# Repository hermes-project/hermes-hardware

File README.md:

# hermes-hardware
# Authors : François Charles, Simon Ménard, Raphaël Outhier

This repository lists all you need if you're interested in the robot hardware's architecture.

What you may find in this repository :

-the 3D models designed with SolidWorks CAD;

-the Eagle CAD PCB schematics and board layout

-the Eagle CAD libraries used

-the datasheets of electronic components

-documentation about how to drive the robot successfully (in French at the moment :p English version to come)

Enjoy your trip among these files ! :)

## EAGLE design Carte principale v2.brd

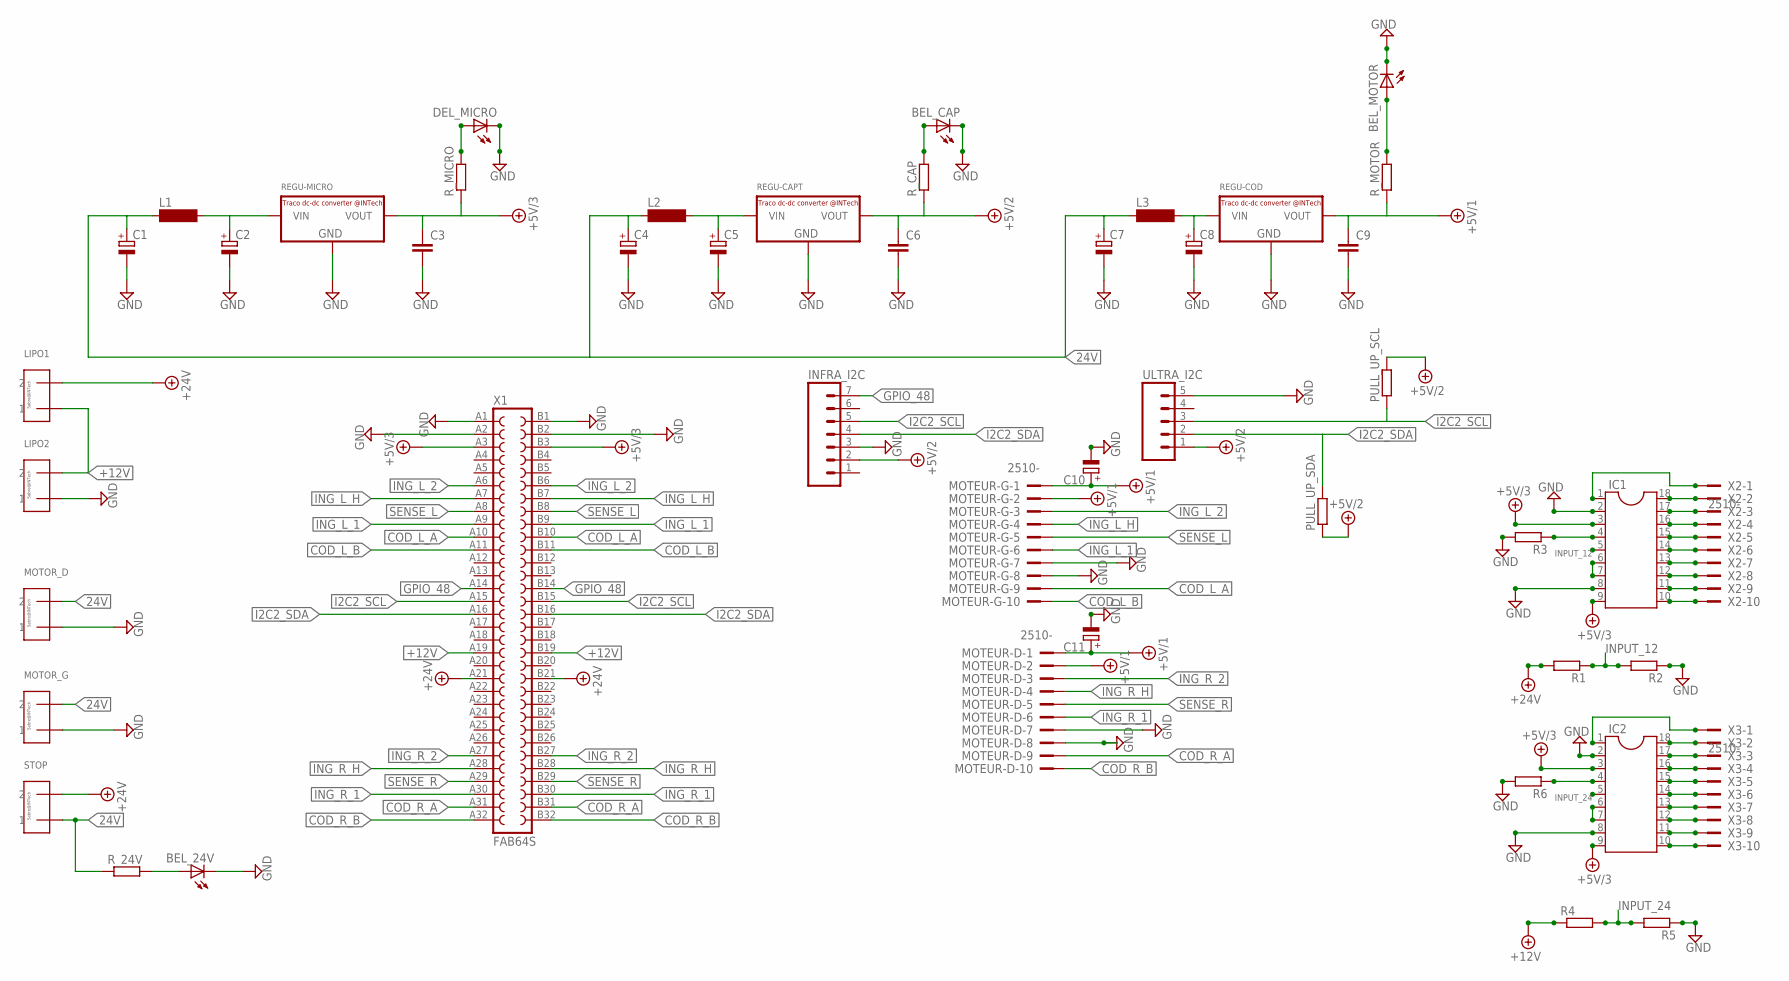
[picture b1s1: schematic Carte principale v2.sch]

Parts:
BEL_24V: LED5MM
BEL_CAP: LED5MM
BEL_MOTOR: LED5MM
C1, C2, C4, C5, C7, C8, C10, C11: CPOL-EUE2.5-6; E2,5-6
C3, C6: C-EU050-025X075; C050-025X075
C9: C5/3; C5B3
DEL_MICRO: LED5MM
IC1, IC2: DIL18S; SOCKET-18
INFRA_I2C: M07; 07P
L1, L2, L3: SD12-1000; SD12_1000
LIPO1, LIPO2: 43160
MOTEUR-D: 2510-; PAK100/2500-10
MOTEUR-G: 2510-; PAK100/2500-10
MOTOR_D: 43160
MOTOR_G: 43160
PULL_UP_SCL: R-EU_0204/7; 0204/7
PULL_UP_SDA: R-EU_0204/7; 0204/7
R1, R2, R3, R4, R5, R6: R-EU_0204/7; 0204/7
REGU-CAPT: R-78C-1.0_INTECH; SIP3_INTECH
REGU-COD: R-78C-1.0_INTECH; SIP3_INTECH
REGU-MICRO: R-78C-1.0_INTECH; SIP3_INTECH
R_24V: R-EU_0204/7; 0204/7
R_CAP: R-EU_0204/7; 0204/7
R_MICRO: R-EU_0204/7; 0204/7
R_MOTOR: R-EU_0204/7; 0204/7
STOP: 43160
ULTRA_I2C: M05; 05P
X1: FAB64S
X2, X3: 2510-; PAK100/2500-10

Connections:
24V: C1.+, C4.+, C7.+, L1.1, L2.1, L3.1, MOTOR_D.2_1 (2), MOTOR_D.2_2 (2), MOTOR_G.2_1 (2), MOTOR_G.2_2 (2), R_24V.1, STOP.1_1 (1), STOP.1_2 (1)
+5V/1: C9.1, C10.+, C11.+, MOTEUR-D.1, MOTEUR-D.2, MOTEUR-G.1, MOTEUR-G.2, REGU-COD.VOUT, R_MOTOR.1
+5V/2: C6.1, INFRA_I2C.2, PULL_UP_SCL.2, PULL_UP_SDA.1, REGU-CAPT.VOUT, R_CAP.1, ULTRA_I2C.1
+5V/3: C3.1, IC1.3, IC1.9, IC2.3, IC2.9, REGU-MICRO.VOUT, R_MICRO.1, X1.A3, X1.B3
+12V: LIPO1.1_1 (1), LIPO1.1_2 (1), LIPO2.2_1 (2), LIPO2.2_2 (2), R4.1, X1.A19, X1.B19
+24V: LIPO1.2_1 (2), LIPO1.2_2 (2), R1.2, STOP.2_1 (2), STOP.2_2 (2), X1.A21, X1.B21
COD_L_A: MOTEUR-G.9, X1.A10, X1.B10
COD_L_B: MOTEUR-G.10, X1.A11, X1.B11
COD_R_A: MOTEUR-D.9, X1.A31, X1.B31
COD_R_B: MOTEUR-D.10, X1.A32, X1.B32
GND: BEL_24V.K (C), BEL_CAP.K (C), BEL_MOTOR.K (C), C1.-, C2.-, C3.2, C4.-, C5.-, C6.2, C7.-, C8.-, C9.2, C10.-, C11.-, DEL_MICRO.K (C), IC1.2, IC1.8, IC2.2, IC2.8, INFRA_I2C.3, LIPO2.1_1 (1), LIPO2.1_2 (1), MOTEUR-D.7, MOTEUR-D.8, MOTEUR-G.7, MOTEUR-G.8, MOTOR_D.1_1 (1), MOTOR_D.1_2 (1), MOTOR_G.1_1 (1), MOTOR_G.1_2 (1), R2.1, R3.2, R5.1, R6.2, REGU-CAPT.GND, REGU-COD.GND, REGU-MICRO.GND, ULTRA_I2C.5, X1.A1, X1.A2, X1.B1, X1.B2
GPIO_48: INFRA_I2C.7, X1.A14, X1.B14
I2C2_SCL: INFRA_I2C.5, PULL_UP_SCL.1, ULTRA_I2C.3, X1.A15, X1.B15
I2C2_SDA: INFRA_I2C.4, PULL_UP_SDA.2, ULTRA_I2C.2, X1.A16, X1.B16
ING_L_1: MOTEUR-G.6, X1.A9, X1.B9
ING_L_2: MOTEUR-G.3, X1.A6, X1.B6
ING_L_H: MOTEUR-G.4, X1.A7, X1.B7
ING_R_1: MOTEUR-D.6, X1.A30, X1.B30
ING_R_2: MOTEUR-D.3, X1.A27, X1.B27
ING_R_H: MOTEUR-D.4, X1.A28, X1.B28
INPUT_12: IC1.5, R1.1, R2.2
INPUT_24: IC2.5, R4.2, R5.2
unnamed: DEL_MICRO.A, R_MICRO.2
unnamed: BEL_24V.A, R_24V.2
unnamed: C8.+, L3.2, REGU-COD.VIN
unnamed: C2.+, L1.2, REGU-MICRO.VIN
unnamed: C5.+, L2.2, REGU-CAPT.VIN
unnamed: BEL_CAP.A, R_CAP.2
unnamed: IC1.6, IC1.7
unnamed: IC1.12, X2.8
unnamed: IC1.13, X2.7
unnamed: BEL_MOTOR.A, R_MOTOR.2
unnamed: IC1.17, X2.3
unnamed: IC1.15, X2.5
unnamed: IC1.14, X2.6
unnamed: IC1.11, X2.9
unnamed: IC1.10, X2.10
unnamed: IC1.16, X2.4
unnamed: IC2.6, IC2.7
unnamed: IC1.18, X2.2
unnamed: IC1.1, X2.1
unnamed: IC2.10, X3.10
unnamed: IC2.11, X3.9
unnamed: IC2.12, X3.8
unnamed: IC2.13, X3.7
unnamed: IC2.14, X3.6
unnamed: IC2.15, X3.5
unnamed: IC2.16, X3.4
unnamed: IC2.17, X3.3
unnamed: IC2.18, X3.2
unnamed: IC2.1, X3.1
unnamed: IC1.4, R3.1
unnamed: IC2.4, R6.1
SENSE_L: MOTEUR-G.5, X1.A8, X1.B8
SENSE_R: MOTEUR-D.5, X1.A29, X1.B29

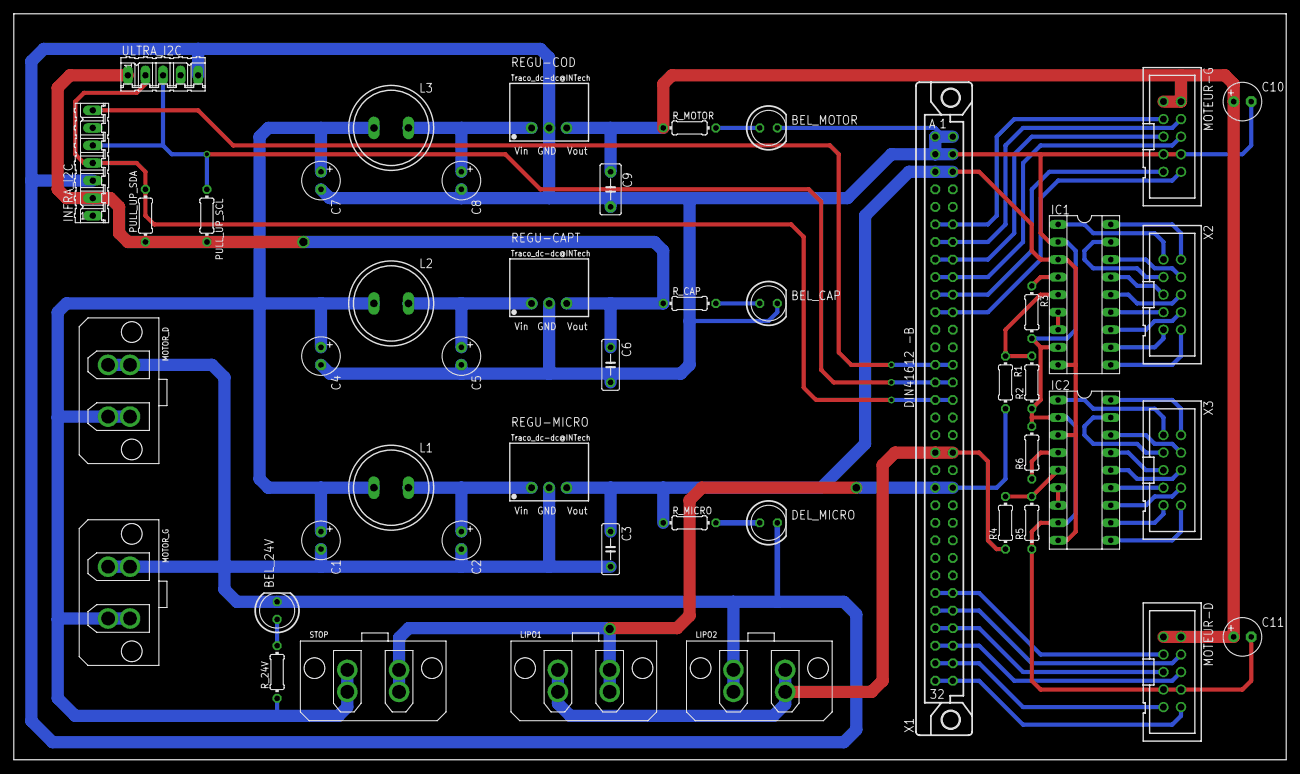
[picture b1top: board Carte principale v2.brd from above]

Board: 2 copper layers, 184.1 x 108.0 mm, 47 parts (0 on the bottom side), 55 nets.

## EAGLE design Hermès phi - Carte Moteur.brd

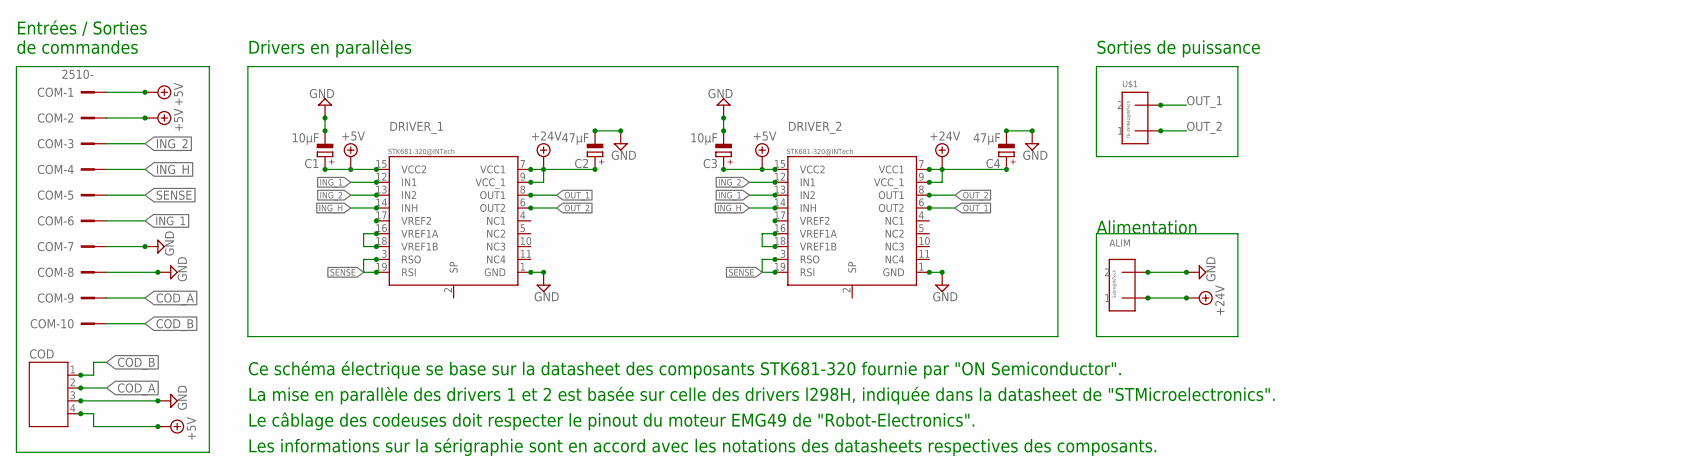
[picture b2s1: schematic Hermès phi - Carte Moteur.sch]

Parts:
ALIM: 43160
C1, C3: 10µF; E2,5-6E
C2, C4: 47µF; E2,5-6E
COD: JST-PH4
COM: 2510-; PAK100/2500-10
DRIVER_1, DRIVER_2: STK681-320
U$1: TE-350942; 350942

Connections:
+5V: C1.+, C3.+, COD.4, COM.1, COM.2, DRIVER_1.15 (VCC2), DRIVER_2.15 (VCC2)
+24V: ALIM.1_1 (1), ALIM.1_2 (1), C2.+, C4.+, DRIVER_1.7 (VCC1), DRIVER_1.9 (VCC_1), DRIVER_2.7 (VCC1), DRIVER_2.9 (VCC_1)
COD_A: COD.2, COM.9
COD_B: COD.1, COM.10
GND: ALIM.2_1 (2), ALIM.2_2 (2), C1.-, C2.-, C3.-, C4.-, COD.3, COM.7, COM.8, DRIVER_1.1 (GND), DRIVER_2.1 (GND)
ING_1: COM.6, DRIVER_1.12 (IN1), DRIVER_2.13 (IN2)
ING_2: COM.3, DRIVER_1.13 (IN2), DRIVER_2.12 (IN1)
ING_H: COM.4, DRIVER_1.14 (INH), DRIVER_2.14 (INH)
unnamed: DRIVER_1.16 (VREF1A), DRIVER_1.18 (VREF1B)
unnamed: DRIVER_2.16 (VREF1A), DRIVER_2.18 (VREF1B)
OUT_1: DRIVER_1.8 (OUT1), DRIVER_2.6 (OUT2), U$1.2
OUT_2: DRIVER_1.6 (OUT2), DRIVER_2.8 (OUT1), U$1.1
SENSE: COM.5, DRIVER_1.3 (RSO), DRIVER_1.19 (RSI), DRIVER_2.3 (RSO), DRIVER_2.19 (RSI)

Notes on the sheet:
Drivers en parallèles
Entrées / Sorties de commandes
Alimentation
Sorties de puissance
Ce schéma électrique se base sur la datasheet des composants STK681-320 fournie par "ON Semiconductor".
La mise en parallèle des drivers 1 et 2 est basée sur celle des drivers l298H, indiquée dans la datasheet de "STMicroelectronics".
Le câblage des codeuses doit respecter le pinout du moteur EMG49 de "Robot-Electronics".
Les informations sur la sérigraphie sont en accord avec les notations des datasheets respectives des composants.

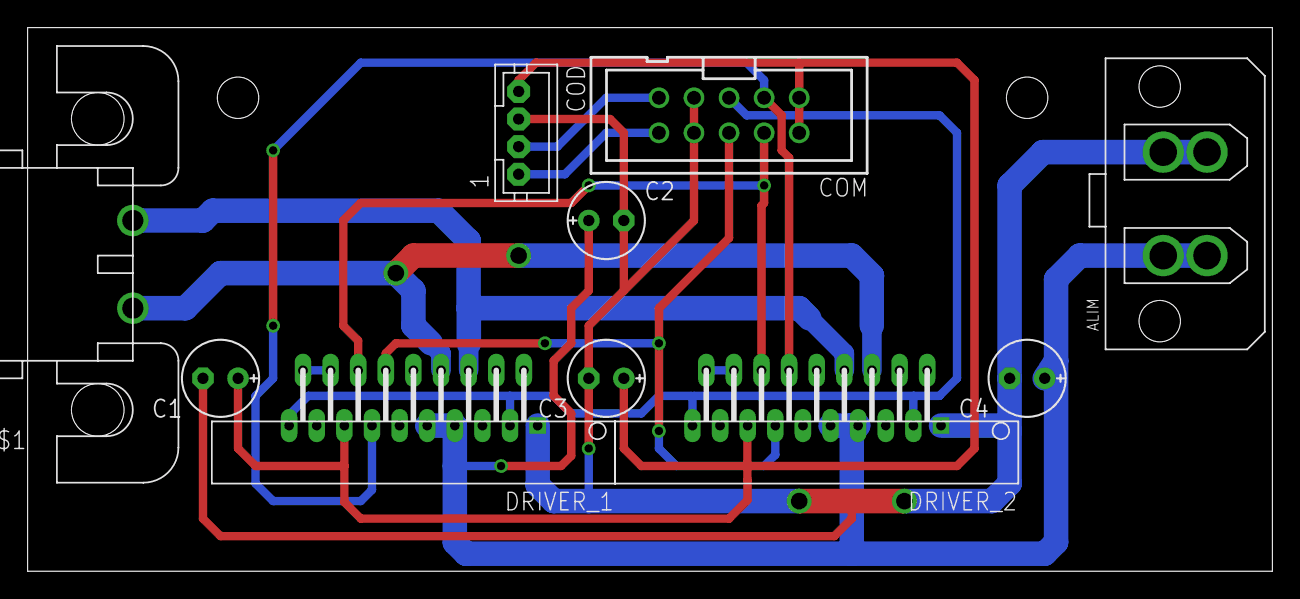
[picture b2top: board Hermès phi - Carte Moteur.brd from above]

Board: 2 copper layers, 90.2 x 39.4 mm, 10 parts (0 on the bottom side), 13 nets.

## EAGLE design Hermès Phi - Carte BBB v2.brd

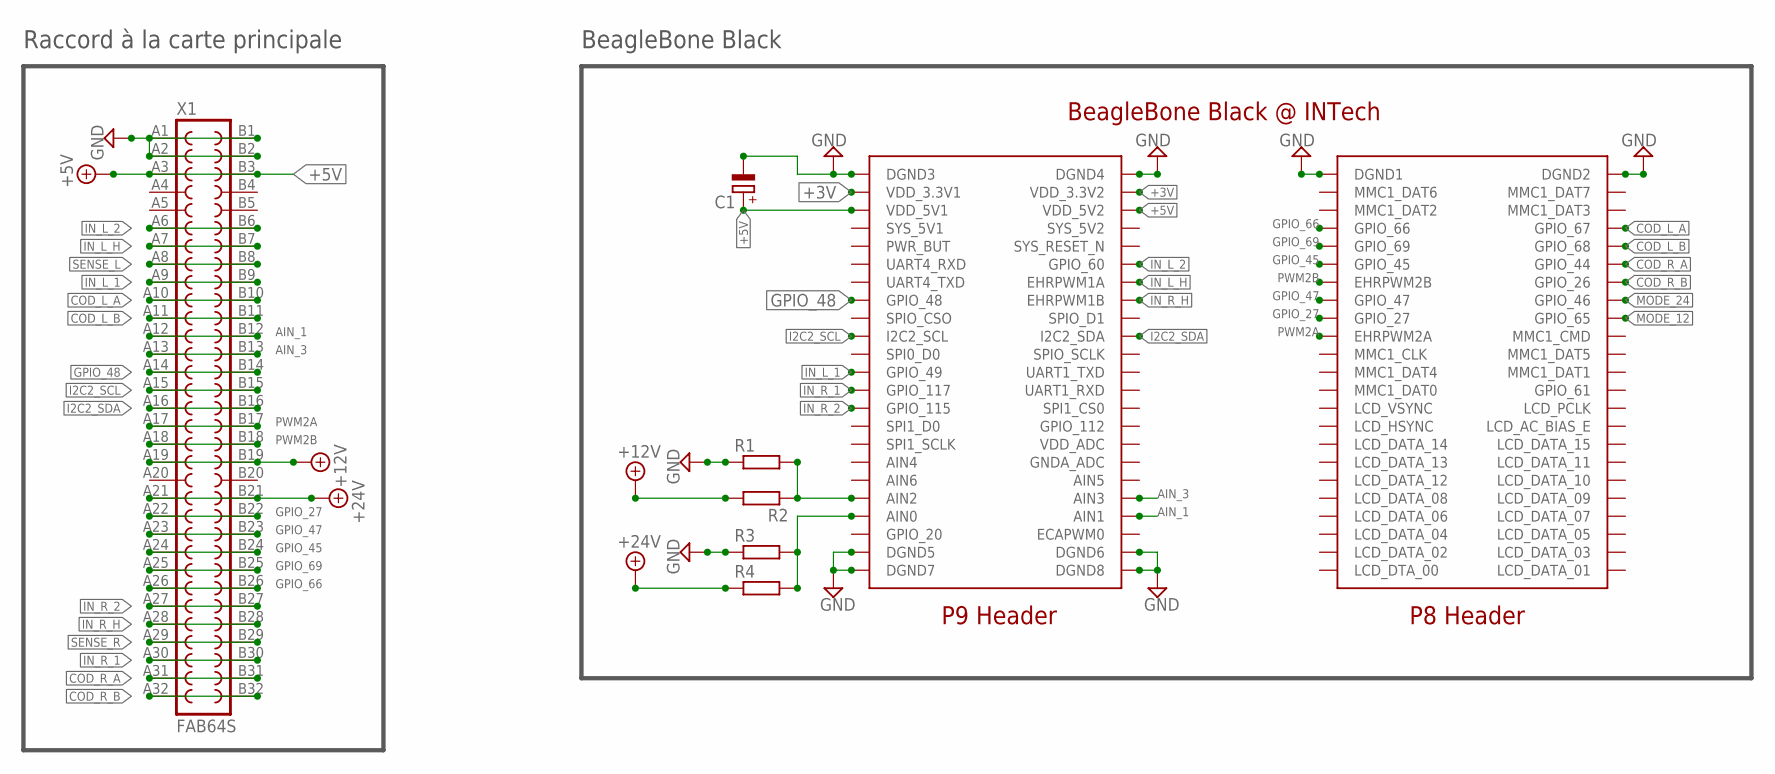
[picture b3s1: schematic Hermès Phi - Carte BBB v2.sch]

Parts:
C1: CPOL-EUE2.5-5; E2,5-5
R1, R2, R3, R4: R-EU_0204/7; 0204/7
U$1: BBB
X1: FAB64S

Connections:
+3V: U$1.VDD_3.3V1, U$1.VDD_3.3V2
+5V: C1.+, U$1.VDD_5V1, U$1.VDD_5V2, X1.A3, X1.B3
+12V: R2.2, X1.A19, X1.B19
+24V: R4.1, X1.A21, X1.B21
AIN_1: U$1.AIN1, X1.A12, X1.B12
AIN_3: U$1.AIN3, X1.A13, X1.B13
COD_L_A: U$1.GPIO_67, X1.A10, X1.B10
COD_L_B: U$1.GPIO_68, X1.A11, X1.B11
COD_R_A: U$1.GPIO_44, X1.A31, X1.B31
COD_R_B: U$1.GPIO_26, X1.A32, X1.B32
GND: C1.-, R1.1, R3.1, U$1.DGND1, U$1.DGND2, U$1.DGND3, U$1.DGND4, U$1.DGND5, U$1.DGND6, U$1.DGND7, U$1.DGND8, X1.A1, X1.A2, X1.B1, X1.B2
GPIO_27: U$1.GPIO_27, X1.A22, X1.B22
GPIO_45: U$1.GPIO_45, X1.A24, X1.B24
GPIO_47: U$1.GPIO_47, X1.A23, X1.B23
GPIO_48: U$1.GPIO_48, X1.A14, X1.B14
GPIO_66: U$1.GPIO_66, X1.A26, X1.B26
GPIO_69: U$1.GPIO_69, X1.A25, X1.B25
I2C2_SCL: U$1.I2C2_SCL, X1.A15, X1.B15
I2C2_SDA: U$1.I2C_SDA (I2C2_SDA), X1.A16, X1.B16
IN_L_1: U$1.GPIO_49, X1.A9, X1.B9
IN_L_2: U$1.GPIO_60, X1.A6, X1.B6
IN_L_H: U$1.EHRPWM1A, X1.A7, X1.B7
IN_R_1: U$1.GPIO_117, X1.A30, X1.B30
IN_R_2: U$1.GPIO_115, X1.A27, X1.B27
IN_R_H: U$1.EHRPWM1B, X1.A28, X1.B28
MODE_12: U$1.GPIO_65
MODE_24: U$1.GPIO_46
unnamed: R3.2, R4.2, U$1.AIN0
unnamed: R1.2, R2.1, U$1.AIN2
PWM2A: U$1.EHRPWM2A, X1.A17, X1.B17
PWM2B: U$1.EHRPWMB2 (EHRPWM2B), X1.A18, X1.B18
SENSE_L: X1.A8, X1.B8
SENSE_R: X1.A29, X1.B29

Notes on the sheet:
Raccord à la carte principale
BeagleBone Black

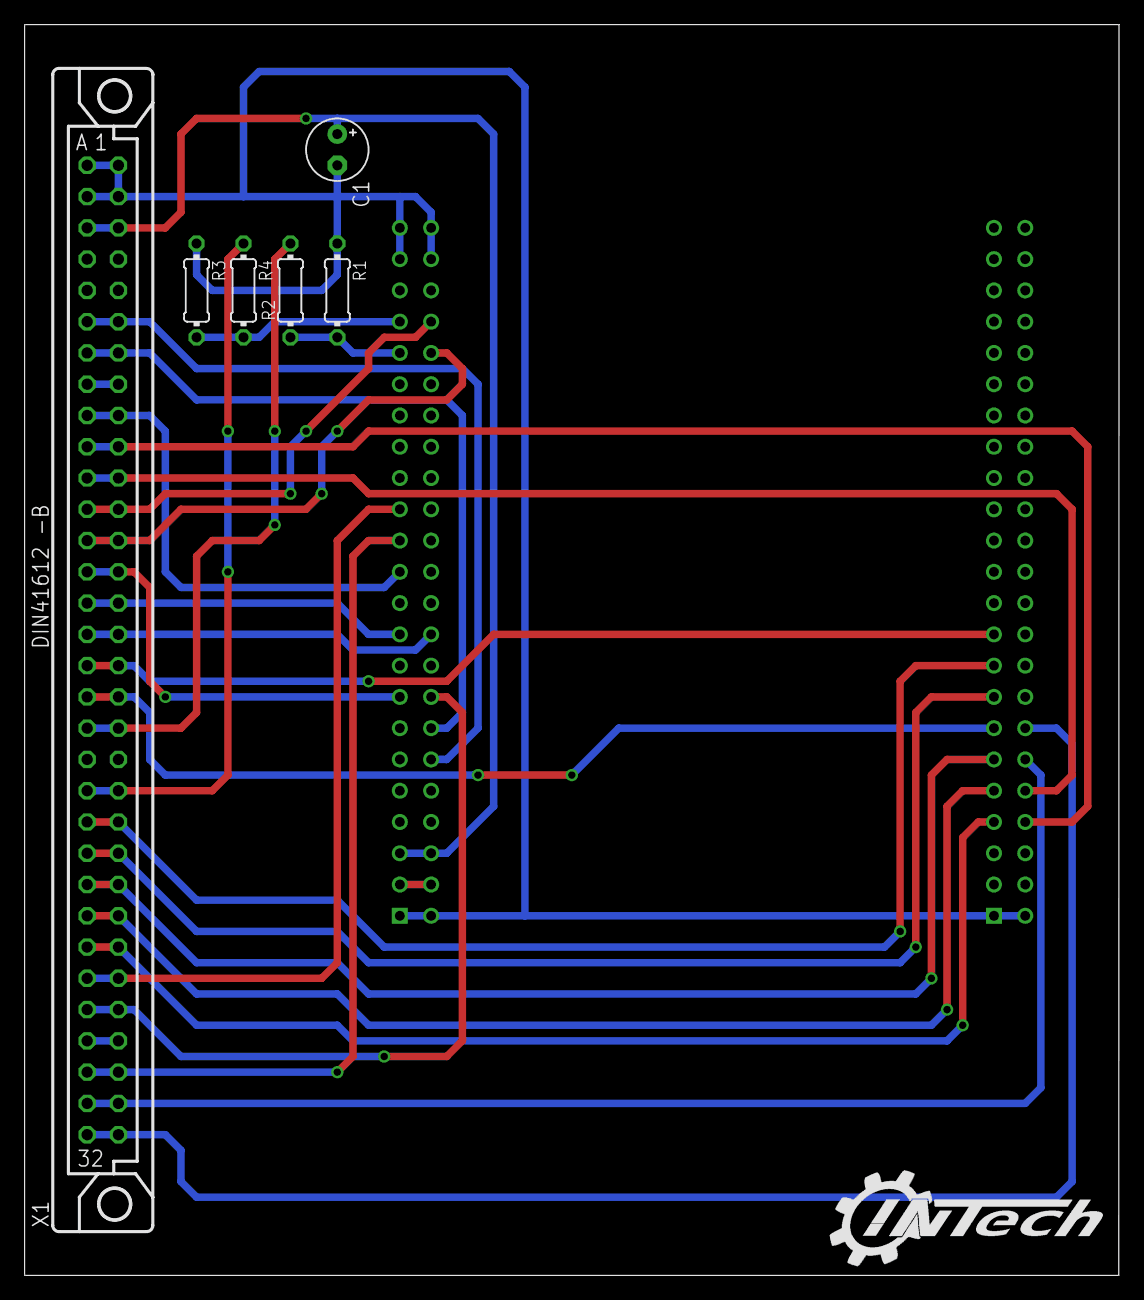
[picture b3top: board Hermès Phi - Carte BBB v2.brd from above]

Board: 2 copper layers, 88.9 x 101.6 mm, 7 parts (1 on the bottom side), 31 nets.
